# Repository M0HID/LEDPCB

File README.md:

# ESP32 LED Matrix Devboard

Here is my PCB for an LED Matrix integrated with a custom ESP32-S3 WROOM-01.
The design includes a USB-C port that can be used to program the chip

## LEDs

There is a 6x6 (total 36) WS2812B 5050 LEDs on the front of the board, which are connected to GPIO21 on the ESP32. 

## Development

An 1x8 header is broken out on the PCB which features a 5v, 3.3v, GND and 5 GPIO pins which can be used for whatever you want to program!

## Gallery

| Front                                                                                         | Back                                                                                        |
|----------------------------------------------------------------------------------------------|----------------------------------------------------------------------------------------------|
|  |  |

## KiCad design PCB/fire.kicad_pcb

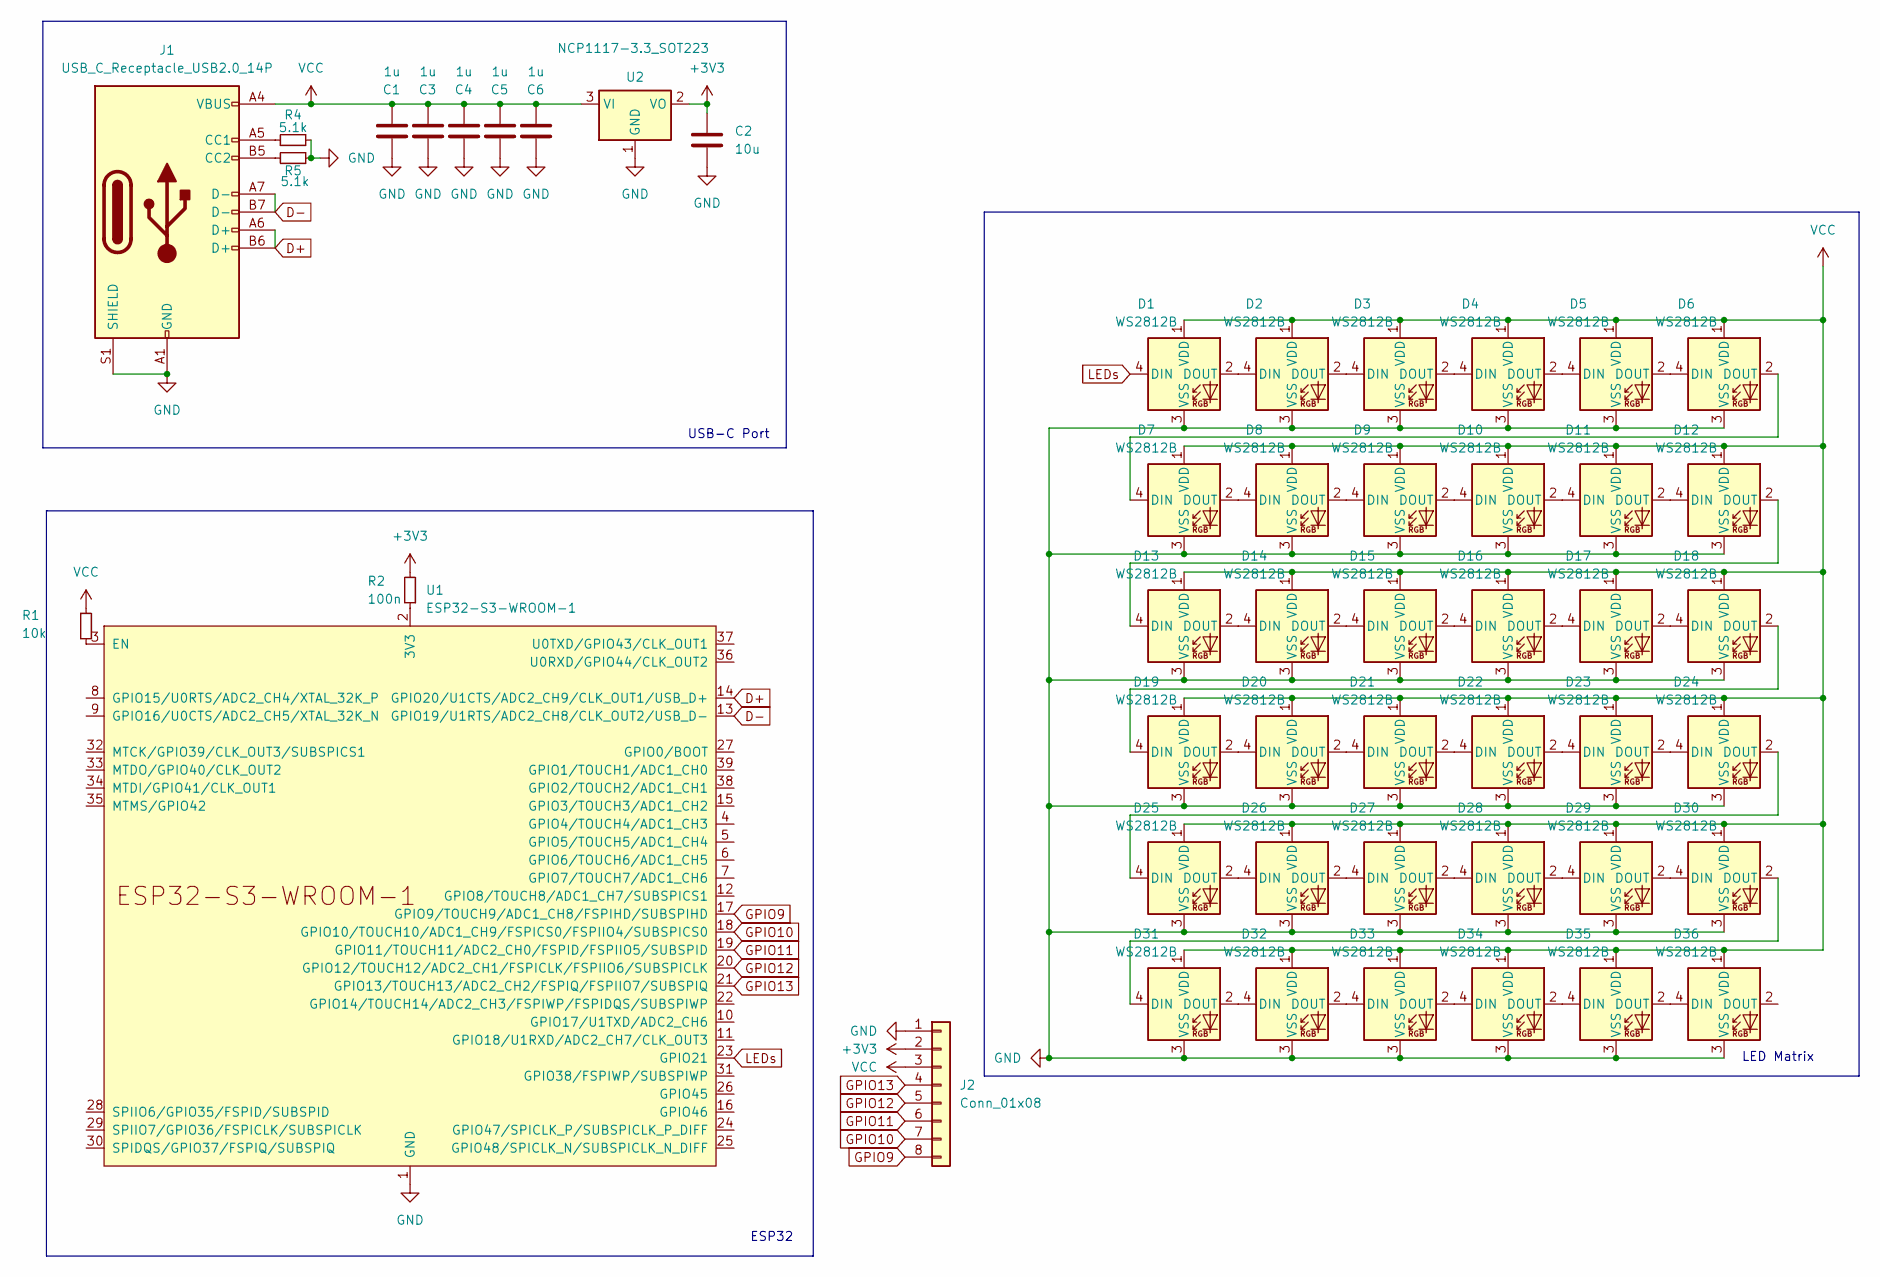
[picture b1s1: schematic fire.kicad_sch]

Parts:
C1, C3, C4, C5, C6: 1u; C_0402_1005Metric
C2: 10u; C_0402_1005Metric
D1, D2, D3, D4, D5, D6, D7, D8, D9, D10, D11, D12, D13, D14, D15, D16, D17, D18, D19, D20, D21, D22, D23, D24, D25, D26, D27, D28, D29, D30, D31, D32, D33, D34, D35, D36: WS2812B; LED_WS2812B_PLCC4_5.0x5.0mm_P3.2mm
J1: USB_C_Receptacle_USB2.0_14P; USB_C_Receptacle_GCT_USB4105-xx-A_16P_TopMnt_Horizontal
J2: Conn_01x08; PinHeader_1x08_P2.54mm_Vertical
R1: 10k; R_0402_1005Metric
R2: 100n; R_0402_1005Metric
R4, R5: 5.1k; R_0402_1005Metric
U1: ESP32-S3-WROOM-1
U2: NCP1117-3.3_SOT223; SOT-223-3_TabPin2

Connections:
+3V3: C2.1, J2.2, R2.2, U2.2 (VO)
D+: J1.A6 (D+), J1.B6 (D+), U1.14 (GPIO20/U1CTS/ADC2_CH9/CLK_OUT1/USB_D+)
D-: J1.A7 (D-), J1.B7 (D-), U1.13 (GPIO19/U1RTS/ADC2_CH8/CLK_OUT2/USB_D-)
GND: C1.1, C2.2, C3.1, C4.1, C5.1, C6.1, D1.3 (VSS), D2.3 (VSS), D3.3 (VSS), D4.3 (VSS), D5.3 (VSS), D6.3 (VSS), D7.3 (VSS), D8.3 (VSS), D9.3 (VSS), D10.3 (VSS), D11.3 (VSS), D12.3 (VSS), D13.3 (VSS), D14.3 (VSS), D15.3 (VSS), D16.3 (VSS), D17.3 (VSS), D18.3 (VSS), D19.3 (VSS), D20.3 (VSS), D21.3 (VSS), D22.3 (VSS), D23.3 (VSS), D24.3 (VSS), D25.3 (VSS), D26.3 (VSS), D27.3 (VSS), D28.3 (VSS), D29.3 (VSS), D30.3 (VSS), D31.3 (VSS), D32.3 (VSS), D33.3 (VSS), D34.3 (VSS), D35.3 (VSS), D36.3 (VSS), J1.A1 (GND), J1.A12 (GND), J1.B1 (GND), J1.B12 (GND), J1.S1 (SHIELD), J2.1, R4.2, R5.1, U1.1 (GND), U1.40 (GND), U1.41 (GND), U2.1 (GND)
GPIO9: J2.8, U1.17 (GPIO9/TOUCH9/ADC1_CH8/FSPIHD/SUBSPIHD)
GPIO10: J2.7, U1.18 (GPIO10/TOUCH10/ADC1_CH9/FSPICS0/FSPIIO4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)
GPIO11: J2.6, U1.19 (GPIO11/TOUCH11/ADC2_CH0/FSPID/FSPIIO5/S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)
GPIO12: J2.5, U1.20 (GPIO12/TOUCH12/ADC2_CH1/FSPICLK/FSPIIO6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)
GPIO13: J2.4, U1.21 (GPIO13/TOUCH13/ADC2_CH2/FSPIQ/FSPIIO7/S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)
LEDs: D1.4 (DIN), U1.23 (GPIO21)
unnamed: D1.2 (DOUT), D2.4 (DIN)
unnamed: D2.2 (DOUT), D3.4 (DIN)
unnamed: D3.2 (DOUT), D4.4 (DIN)
unnamed: D4.2 (DOUT), D5.4 (DIN)
unnamed: D5.2 (DOUT), D6.4 (DIN)
unnamed: D6.2 (DOUT), D7.4 (DIN)
unnamed: D7.2 (DOUT), D8.4 (DIN)
unnamed: D8.2 (DOUT), D9.4 (DIN)
unnamed: D9.2 (DOUT), D10.4 (DIN)
unnamed: D10.2 (DOUT), D11.4 (DIN)
unnamed: D11.2 (DOUT), D12.4 (DIN)
unnamed: D12.2 (DOUT), D13.4 (DIN)
unnamed: D13.2 (DOUT), D14.4 (DIN)
unnamed: D14.2 (DOUT), D15.4 (DIN)
unnamed: D15.2 (DOUT), D16.4 (DIN)
unnamed: D16.2 (DOUT), D17.4 (DIN)
unnamed: D17.2 (DOUT), D18.4 (DIN)
unnamed: D18.2 (DOUT), D19.4 (DIN)
unnamed: D19.2 (DOUT), D20.4 (DIN)
unnamed: D20.2 (DOUT), D21.4 (DIN)
unnamed: D21.2 (DOUT), D22.4 (DIN)
unnamed: D22.2 (DOUT), D23.4 (DIN)
unnamed: D23.2 (DOUT), D24.4 (DIN)
unnamed: D24.2 (DOUT), D25.4 (DIN)
unnamed: D25.2 (DOUT), D26.4 (DIN)
unnamed: D26.2 (DOUT), D27.4 (DIN)
unnamed: D27.2 (DOUT), D28.4 (DIN)
unnamed: D28.2 (DOUT), D29.4 (DIN)
unnamed: D29.2 (DOUT), D30.4 (DIN)
unnamed: D30.2 (DOUT), D31.4 (DIN)
unnamed: D31.2 (DOUT), D32.4 (DIN)
unnamed: D32.2 (DOUT), D33.4 (DIN)
unnamed: D33.2 (DOUT), D34.4 (DIN)
unnamed: D34.2 (DOUT), D35.4 (DIN)
unnamed: D35.2 (DOUT), D36.4 (DIN)
unnamed: J1.A5 (CC1), R4.1
unnamed: J1.B5 (CC2), R5.2
unnamed: R2.1, U1.2 (3V3)
unnamed: R1.2, U1.3 (EN)
VCC: C1.2, C3.2, C4.2, C5.2, C6.2, D1.1 (VDD), D2.1 (VDD), D3.1 (VDD), D4.1 (VDD), D5.1 (VDD), D6.1 (VDD), D7.1 (VDD), D8.1 (VDD), D9.1 (VDD), D10.1 (VDD), D11.1 (VDD), D12.1 (VDD), D13.1 (VDD), D14.1 (VDD), D15.1 (VDD), D16.1 (VDD), D17.1 (VDD), D18.1 (VDD), D19.1 (VDD), D20.1 (VDD), D21.1 (VDD), D22.1 (VDD), D23.1 (VDD), D24.1 (VDD), D25.1 (VDD), D26.1 (VDD), D27.1 (VDD), D28.1 (VDD), D29.1 (VDD), D30.1 (VDD), D31.1 (VDD), D32.1 (VDD), D33.1 (VDD), D34.1 (VDD), D35.1 (VDD), D36.1 (VDD), J1.A4 (VBUS), J1.A9 (VBUS), J1.B4 (VBUS), J1.B9 (VBUS), J2.3, R1.1, U2.3 (VI)

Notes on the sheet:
USB-C Port
LED Matrix
ESP32

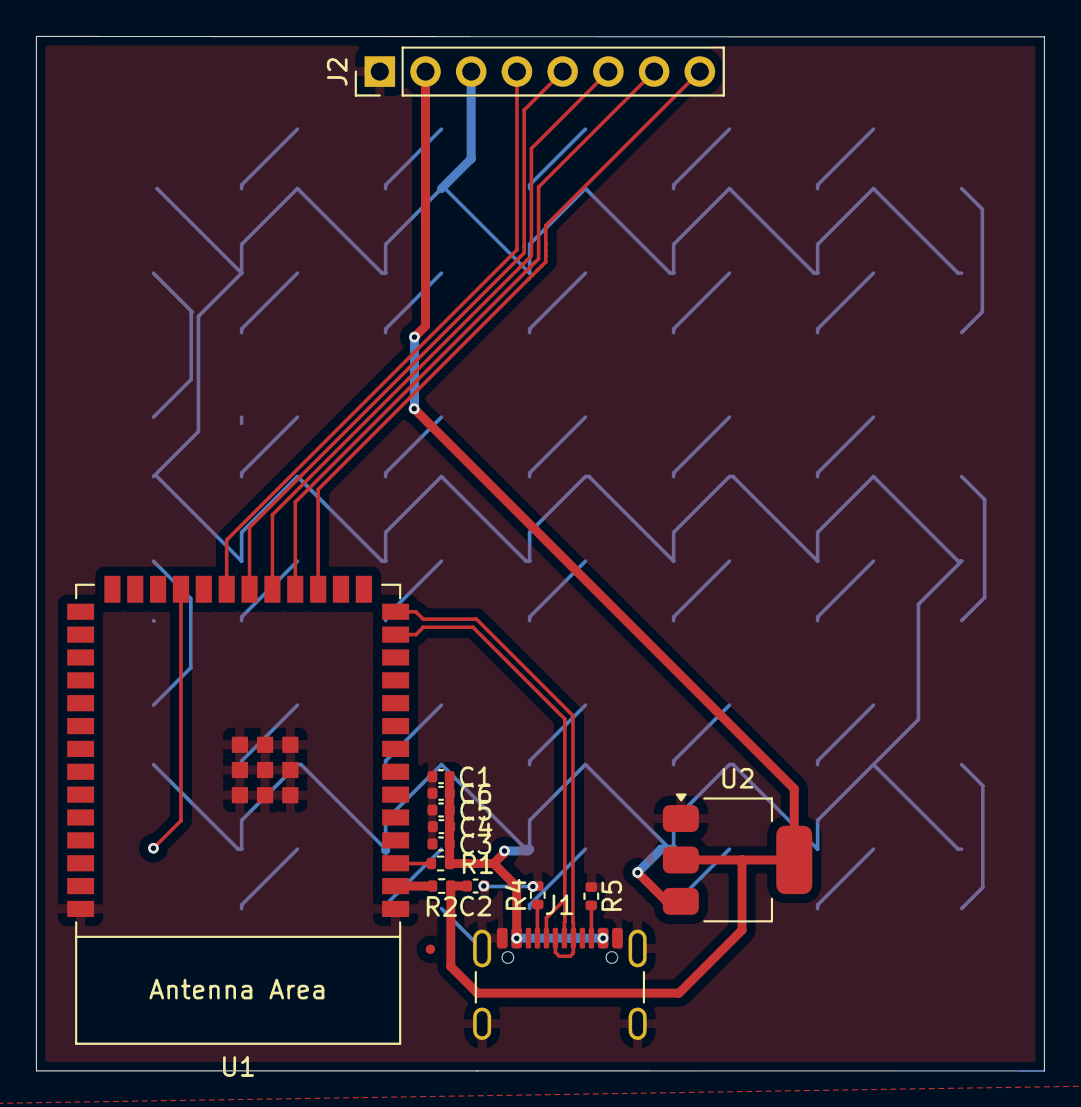
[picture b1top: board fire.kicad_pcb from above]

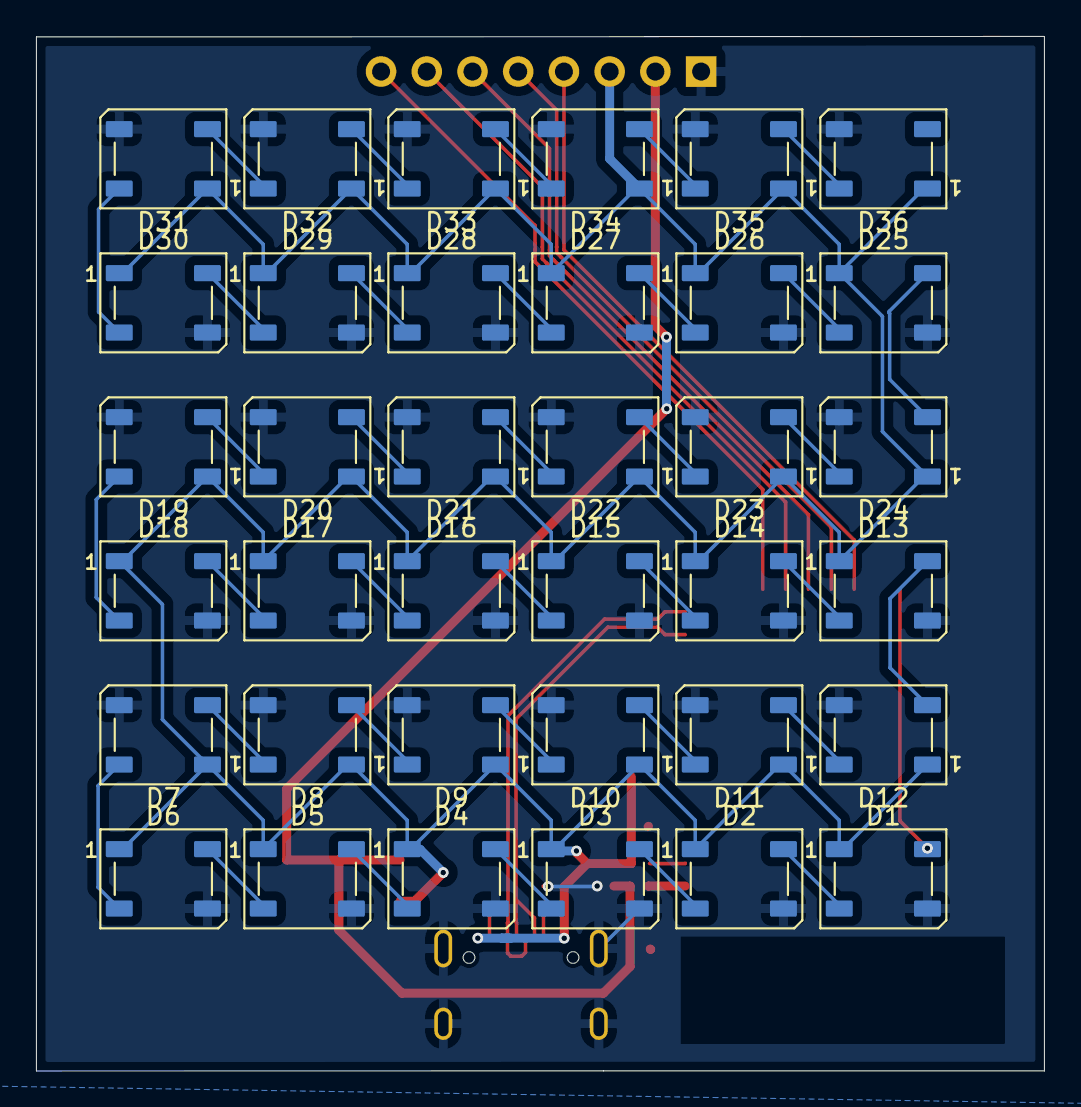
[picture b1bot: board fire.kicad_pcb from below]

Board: 2 copper layers, 56.0 x 57.5 mm, 50 parts (36 on the bottom side), 50 nets.

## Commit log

2025-01-13 upload
